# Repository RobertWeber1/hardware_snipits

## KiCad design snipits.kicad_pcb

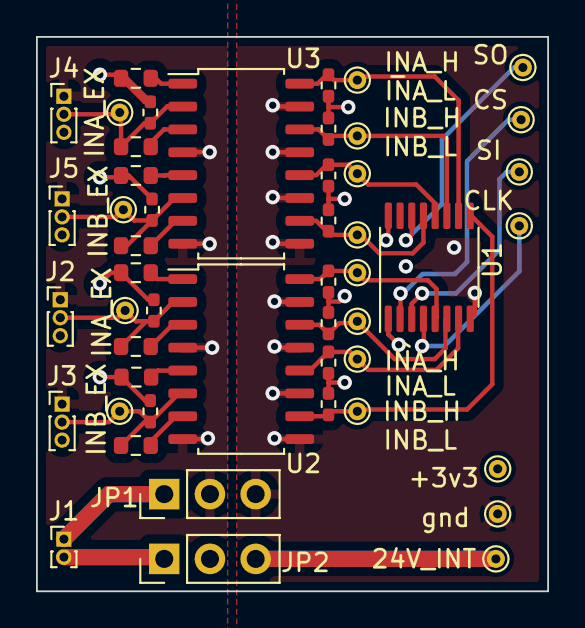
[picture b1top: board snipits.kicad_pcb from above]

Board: 4 copper layers, 28.4 x 30.8 mm, 49 parts (0 on the bottom side), 31 nets.

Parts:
J1: Conn_01x02; PinHeader_1x02_P1.00mm_Vertical
J2, J3, J4, J5: Conn_01x03; PinHeader_1x03_P1.00mm_Vertical
JP1, JP2: Jumper_3_Open; PinHeader_1x03_P2.54mm_Vertical
R11, R14, R15, R16, R19, R20, R21, R22, R27, R28, R29, R30: 47k; R_0402_1005Metric_Pad0.72x0.64mm_HandSolder
R12, R13, R17, R18, R23, R24, R25, R26: 800; R_0603_1608Metric
TP1, TP7: INA_EX; TestPoint_THTPad_D1.0mm_Drill0.5mm
TP2, TP9: INA_H; TestPoint_THTPad_D1.0mm_Drill0.5mm
TP3, TP10: INA_L; TestPoint_THTPad_D1.0mm_Drill0.5mm
TP4, TP8: INB_EX; TestPoint_THTPad_D1.0mm_Drill0.5mm
TP5, TP11: INB_H; TestPoint_THTPad_D1.0mm_Drill0.5mm
TP6, TP12: INB_L; TestPoint_THTPad_D1.0mm_Drill0.5mm
TP13: 24V_INT; TestPoint_THTPad_D1.0mm_Drill0.5mm
TP14: CS; TestPoint_THTPad_D1.0mm_Drill0.5mm
TP15: SI; TestPoint_THTPad_D1.0mm_Drill0.5mm
TP16: CLK; TestPoint_THTPad_D1.0mm_Drill0.5mm
TP17: SO; TestPoint_THTPad_D1.0mm_Drill0.5mm
TP18: +3v3; TestPoint_THTPad_D1.0mm_Drill0.5mm
TP19: gnd; TestPoint_THTPad_D1.0mm_Drill0.5mm
U1: 74VHC9164FT; TSSOP-16_4.4x5mm_P0.65mm
U2, U3: TLP291-4; SOIC-16_4.55x10.3mm_P1.27mm

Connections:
+3V3: R14.1, R15.1, R19.1, R20.1, R27.1, R28.1, R29.1, R30.1, TP18.1, U1.1 (P/S_CONT), U1.16 (VCC)
/isolated_multi_input/input1/INA: J4.2, R21.2, R24.1, TP7.1, U3.2
/isolated_multi_input/input1/INA_HIGH: R27.2, TP9.1, U1.10 (Q/D5), U3.16
/isolated_multi_input/input1/INA_LOW: R28.2, TP10.1, U1.11 (Q/D6), U3.14
/isolated_multi_input/input1/INB: J5.2, R22.2, R26.1, TP8.1, U3.6
/isolated_multi_input/input1/INB_HIGH: R29.2, TP11.1, U1.12 (Q/D7), U3.12
/isolated_multi_input/input1/INB_LOW: R30.2, TP12.1, U1.13 (Q/D8), U3.10
/isolated_multi_input/input/INA: J2.2, R11.2, R13.1, TP1.1, U2.2
/isolated_multi_input/input/INA_HIGH: R14.2, TP2.1, U1.5 (Q/D1), U2.16
/isolated_multi_input/input/INA_LOW: R15.2, TP3.1, U1.6 (Q/D2), U2.14
/isolated_multi_input/input/INB: J3.2, R16.2, R18.1, TP4.1, U2.6
/isolated_multi_input/input/INB_HIGH: R19.2, TP5.1, U1.7 (Q/D3), U2.12
/isolated_multi_input/input/INB_LOW: R20.2, TP6.1, U1.9 (Q/D4), U2.10
/isolated_multi_input/input/gnd_ext: J2.1, J3.1, J4.1, J5.1, JP1.2 (C), U2.4, U2.8, U3.4, U3.8
/isolated_multi_input/input/vdd_ext: J2.3, J3.3, J4.3, J5.3, JP2.2 (C), R11.1, R12.1, R16.1, R17.1, R21.1, R22.1, R23.1, R25.1
GND: JP1.3 (B), TP19.1, U1.8 (GND), U2.9, U2.11, U2.13, U2.15, U3.9, U3.11, U3.13, U3.15
unnamed: J1.1, JP1.1 (A)
unnamed: J1.2, JP2.1 (A)
unnamed: JP2.3 (B), TP13.1
unnamed: R12.2, U2.1
unnamed: R13.2, U2.3
unnamed: R17.2, U2.5
unnamed: R18.2, U2.7
unnamed: R23.2, U3.1
unnamed: R24.2, U3.3
unnamed: R25.2, U3.5
unnamed: R26.2, U3.7
unnamed: TP14.1, U1.2 (~CLR_LOAD)
unnamed: TP15.1, U1.3 (SI)
unnamed: TP16.1, U1.4 (CK)
unnamed: TP17.1, U1.14 (Q8')
